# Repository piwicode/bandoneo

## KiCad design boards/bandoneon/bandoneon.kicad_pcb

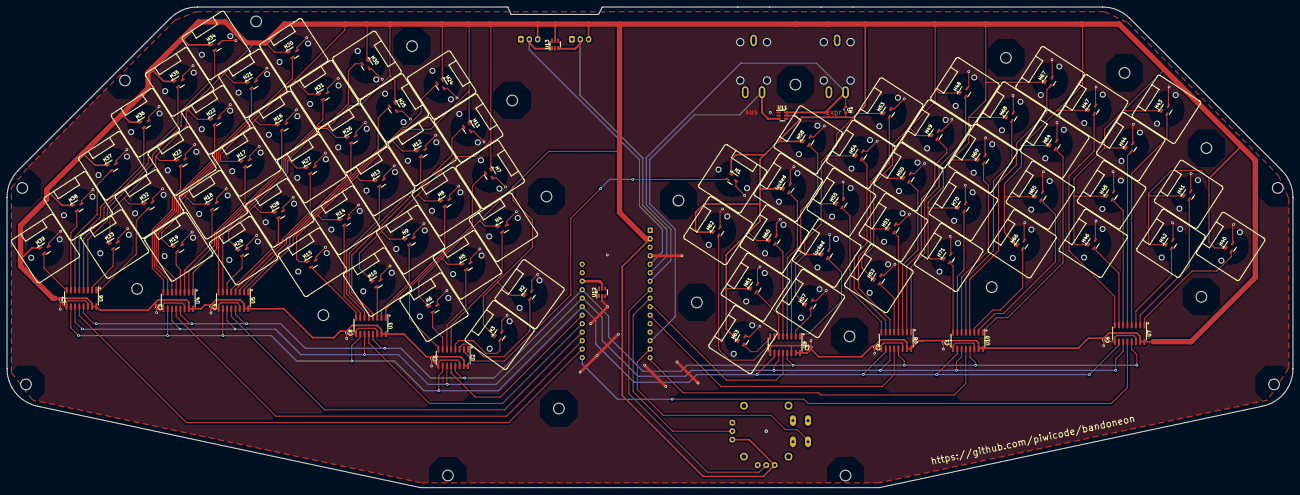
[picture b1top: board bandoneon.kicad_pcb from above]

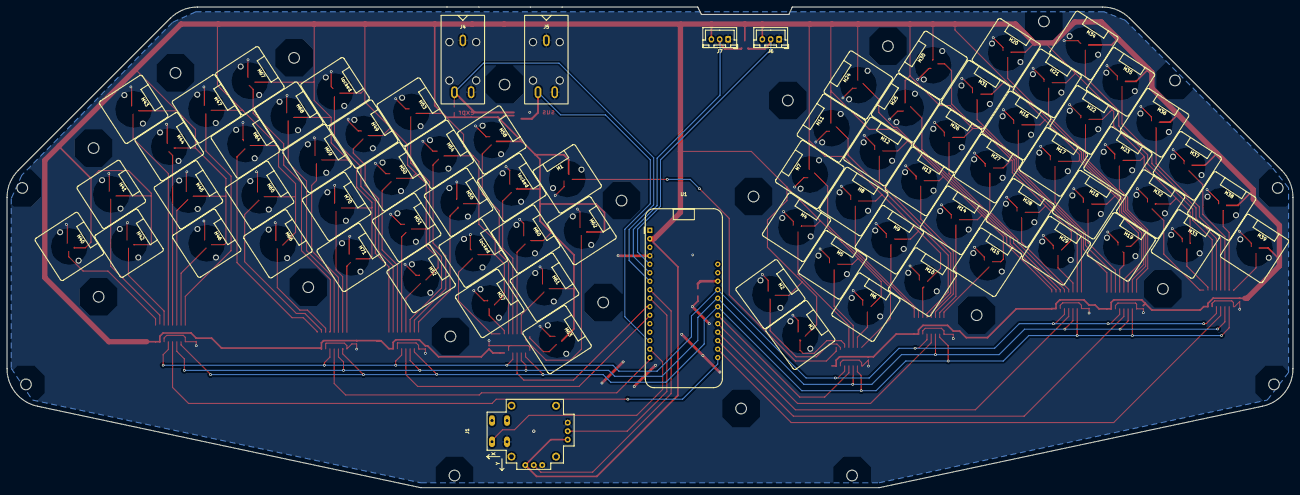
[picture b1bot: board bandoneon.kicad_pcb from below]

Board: 2 copper layers, 384.9 x 143.8 mm, 122 parts (6 on the bottom side), 93 nets.

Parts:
C1, C2, C3, C4, C5, C6, C7, C8, C9: 1uF; C_0402_1005Metric
H1, H2, H3, H4, H5, H6, H7, H8, H9, H10, H11, H12, H13, H14, H15, H16, H17, H18, H19, H20, H21, H22, H23, H24, H25, H26, H27, H28, H29, H30, H31, H32, H33, H34, H35, H36, H37, H38, H39, H40, H41, H42, H43, H44, H45, H46, H47, H48, H49, H50, H51, H52, H53, H54, H55, H57, H58, H60, H61, H62, H63, H64, H65, H66, H67, H68, H69, H70, H71: SS39ET; SOT-23_SS39ET
J1: 2D JOYSTICK; Adafruit (512) Analog 2-axis Thumb Joystick with Select But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
J4, J5: AudioJack3; Jack TRS
J6, J7: JST XH-3A; JST_XH_B3B-XH-A_1x03_P2.50mm_Vertical
MH01, MH02, MH03, MH05, MH06, MH07, MH08, MH09, MH10, MH11, MH12, MH13, MH14, MH15, MH16, MH17, MH18, MH19, MH20, MH21, MH22, MH33, MH39: MountingHole_3.2mm_M3_large
R1: 10K; R_0603_1608Metric
U1: Feather M4 Express; Adafruit_Feather_M4_Express
U2, U3, U4, U5, U6, U7, U8, U9, U10: MCP3008; SOIC-16_MCP3008T-I_SL
U11, U12, U13: SRV05-4; SOT-23-6
locked: SS39ET; SOT-23_SS39ET
locked#2: locked; SOT-23_SS39ET

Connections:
+3.3V: C1.1, C2.1, C3.1, C4.1, C5.1, C6.1, C7.1, C8.1, C9.1, H1.1 (VCC), H2.1 (VCC), H3.1 (VCC), H4.1 (VCC), H5.1 (VCC), H6.1 (VCC), H7.1 (VCC), H8.1 (VCC), H9.1 (VCC), H10.1 (VCC), H11.1 (VCC), H12.1 (VCC), H13.1 (VCC), H14.1 (VCC), H15.1 (VCC), H16.1 (VCC), H17.1 (VCC), H18.1 (VCC), H19.1 (VCC), H20.1 (VCC), H21.1 (VCC), H22.1 (VCC), H23.1 (VCC), H24.1 (VCC), H25.1 (VCC), H26.1 (VCC), H27.1 (VCC), H28.1 (VCC), H29.1 (VCC), H30.1 (VCC), H31.1 (VCC), H32.1 (VCC), H33.1 (VCC), H34.1 (VCC), H35.1 (VCC), H36.1 (VCC), H37.1 (VCC), H38.1 (VCC), H39.1 (VCC), H40.1 (VCC), H41.1 (VCC), H42.1 (VCC), H43.1 (VCC), H44.1 (VCC), H45.1 (VCC), H46.1 (VCC), H47.1 (VCC), H48.1 (VCC), H49.1 (VCC), H50.1 (VCC), H51.1 (VCC), H52.1 (VCC), H53.1 (VCC), H54.1 (VCC), H55.1 (VCC), H57.1 (VCC), H58.1 (VCC), H60.1 (VCC), H61.1 (VCC), H62.1 (VCC), H63.1 (VCC), H64.1 (VCC), H65.1 (VCC), H66.1 (VCC), H67.1 (VCC), H68.1 (VCC), H69.1 (VCC), H70.1 (VCC), H71.1 (VCC), J1.2 (X+), J1.5 (Y+), J6.3, J7.3, R1.2, U1.2 (3.3V), U2.15 (Vref), U2.16 (Vdd), U3.15 (Vref), U3.16 (Vdd), U4.15 (Vref), U4.16 (Vdd), U5.15 (Vref), U5.16 (Vdd), U6.15 (Vref), U6.16 (Vdd), U7.15 (Vref), U7.16 (Vdd), U8.15 (Vref), U8.16 (Vdd), U9.15 (Vref), U9.16 (Vdd), U10.15 (Vref), U10.16 (Vdd), U11.5 (VP), U13.5 (VP), locked.1 (VCC), locked#2.1 (VCC)
/CLK: U1.25 ((13)PA23), U2.13 (CLK), U3.13 (CLK), U4.13 (CLK), U5.13 (CLK), U6.13 (CLK), U7.13 (CLK), U8.13 (CLK), U9.13 (CLK), U10.13 (CLK)
/CS: U1.23 ((11)PA21), U2.10 (~CS/SHDN), U3.10 (~CS/SHDN), U4.10 (~CS/SHDN), U5.10 (~CS/SHDN), U6.10 (~CS/SHDN), U7.10 (~CS/SHDN), U8.10 (~CS/SHDN), U9.10 (~CS/SHDN), U10.10 (~CS/SHDN)
/EXPR_PED: J4.T, R1.1, U1.7 (PB08(16/A2)), U11.6 (IO4)
/G1/MISO: U1.22 ((10)PA20), U2.12 (Dout)
/G2/MISO: U1.21 ((9)PA19), U3.12 (Dout)
/G3/MISO: U1.19 ((5)PA16), U4.12 (Dout)
/G4/MISO: U1.20 ((6)PA18), U5.12 (Dout)
/G5/MISO: U1.18 ((22)PA13), U6.12 (Dout)
/G6/MISO: U1.16 (PA14(4)), U10.12 (Dout)
/G7/MISO: U1.10 (PA06(19/A5)), U9.12 (Dout)
/G9/MISO: U1.17 ((21)PA12), U7.12 (Dout)
/G10/MISO: U1.11 (PA17(25)), U8.12 (Dout)
/JOY_BT: J1.7 (BTN+), U1.15 (PB16(1))
/JOY_X: J1.1 (X), U1.8 (PB09(17/A3))
/JOY_Y: J1.4 (Y), U1.9 (PA04(18/A4))
/MOSI: U1.24 ((12)PA22), U2.11 (Din), U3.11 (Din), U4.11 (Din), U5.11 (Din), U6.11 (Din), U7.11 (Din), U8.11 (Din), U9.11 (Din), U10.11 (Din)
/P1: J7.2, U1.6 (PA05(15/A1)), U13.3 (IO2)
/P2: J6.2, U1.5 (PA02(14/A0)), U13.1 (IO1)
/SUS_PED: J5.T, U1.14 (PB17(0)), U11.3 (IO2)
/VBUS: U1.26 (VBUS), U12.5 (VP)
GND: C1.2, C2.2, C3.2, C4.2, C5.2, C6.2, C7.2, C8.2, C9.2, H1.3 (GND), H2.3 (GND), H3.3 (GND), H4.3 (GND), H5.3 (GND), H6.3 (GND), H7.3 (GND), H8.3 (GND), H9.3 (GND), H10.3 (GND), H11.3 (GND), H12.3 (GND), H13.3 (GND), H14.3 (GND), H15.3 (GND), H16.3 (GND), H17.3 (GND), H18.3 (GND), H19.3 (GND), H20.3 (GND), H21.3 (GND), H22.3 (GND), H23.3 (GND), H24.3 (GND), H25.3 (GND), H26.3 (GND), H27.3 (GND), H28.3 (GND), H29.3 (GND), H30.3 (GND), H31.3 (GND), H32.3 (GND), H33.3 (GND), H34.3 (GND), H35.3 (GND), H36.3 (GND), H37.3 (GND), H38.3 (GND), H39.3 (GND), H40.3 (GND), H41.3 (GND), H42.3 (GND), H43.3 (GND), H44.3 (GND), H45.3 (GND), H46.3 (GND), H47.3 (GND), H48.3 (GND), H49.3 (GND), H50.3 (GND), H51.3 (GND), H52.3 (GND), H53.3 (GND), H54.3 (GND), H55.3 (GND), H57.3 (GND), H58.3 (GND), H60.3 (GND), H61.3 (GND), H62.3 (GND), H63.3 (GND), H64.3 (GND), H65.3 (GND), H66.3 (GND), H67.3 (GND), H68.3 (GND), H69.3 (GND), H70.3 (GND), H71.3 (GND), J1.0 (X-), J1.3 (Y-), J1.6 (BTN-), J4.R, J4.S, J5.R, J5.S, J6.1, J7.1, U1.4 (GND), U2.9 (DGND), U2.14 (AGND), U3.9 (DGND), U3.14 (AGND), U4.9 (DGND), U4.14 (AGND), U5.9 (DGND), U5.14 (AGND), U6.9 (DGND), U6.14 (AGND), U7.9 (DGND), U7.14 (AGND), U8.9 (DGND), U8.14 (AGND), U9.9 (DGND), U9.14 (AGND), U10.9 (DGND), U10.14 (AGND), U11.2 (VN), U12.2 (VN), U13.2 (VN), locked.3 (GND), locked#2.3 (GND)
unnamed: H1.2 (OUT), U2.2 (CH1)
unnamed: H2.2 (OUT), U2.3 (CH2)
unnamed: H3.2 (OUT), U2.4 (CH3)
unnamed: H4.2 (OUT), U2.5 (CH4)
unnamed: H5.2 (OUT), U2.6 (CH5)
unnamed: H6.2 (OUT), U2.7 (CH6)
unnamed: H7.2 (OUT), U2.8 (CH7)
unnamed: H8.2 (OUT), U3.1 (CH0)
unnamed: H9.2 (OUT), U3.2 (CH1)
unnamed: H10.2 (OUT), U3.3 (CH2)
unnamed: H11.2 (OUT), U3.4 (CH3)
unnamed: H12.2 (OUT), U3.5 (CH4)
unnamed: H13.2 (OUT), U3.6 (CH5)
unnamed: H14.2 (OUT), U3.7 (CH6)
unnamed: H15.2 (OUT), U3.8 (CH7)
unnamed: H16.2 (OUT), U4.1 (CH0)
unnamed: H17.2 (OUT), U4.2 (CH1)
unnamed: H18.2 (OUT), U4.3 (CH2)
unnamed: H19.2 (OUT), U4.4 (CH3)
unnamed: H20.2 (OUT), U4.5 (CH4)
unnamed: H21.2 (OUT), U4.6 (CH5)
unnamed: H22.2 (OUT), U4.7 (CH6)
unnamed: H23.2 (OUT), U4.8 (CH7)
unnamed: H24.2 (OUT), U5.1 (CH0)
unnamed: H25.2 (OUT), U5.2 (CH1)
unnamed: H26.2 (OUT), U5.3 (CH2)
unnamed: H27.2 (OUT), U5.4 (CH3)
unnamed: H28.2 (OUT), U5.5 (CH4)
unnamed: H29.2 (OUT), U5.6 (CH5)
unnamed: H30.2 (OUT), U5.7 (CH6)
unnamed: H31.2 (OUT), U5.8 (CH7)
unnamed: H32.2 (OUT), U6.1 (CH0)
unnamed: H33.2 (OUT), U6.2 (CH1)
unnamed: H34.2 (OUT), U6.3 (CH2)
unnamed: H35.2 (OUT), U6.4 (CH3)
unnamed: H36.2 (OUT), U6.5 (CH4)
unnamed: H37.2 (OUT), U6.6 (CH5)
unnamed: H38.2 (OUT), U6.7 (CH6)
unnamed: H39.2 (OUT), U6.8 (CH7)
unnamed: H40.2 (OUT), U7.1 (CH0)
unnamed: H41.2 (OUT), U7.2 (CH1)
unnamed: H42.2 (OUT), U7.3 (CH2)
unnamed: H43.2 (OUT), U7.4 (CH3)
unnamed: H44.2 (OUT), U7.5 (CH4)
unnamed: H45.2 (OUT), U7.6 (CH5)
unnamed: H46.2 (OUT), U7.7 (CH6)
unnamed: H47.2 (OUT), U7.8 (CH7)
unnamed: H48.2 (OUT), U8.1 (CH0)
unnamed: H49.2 (OUT), U8.2 (CH1)
unnamed: H50.2 (OUT), U8.3 (CH2)
unnamed: H51.2 (OUT), U8.4 (CH3)
unnamed: H52.2 (OUT), U8.5 (CH4)
unnamed: H53.2 (OUT), U8.6 (CH5)
unnamed: H54.2 (OUT), U8.7 (CH6)
unnamed: H55.2 (OUT), U8.8 (CH7)
unnamed: U9.1 (CH0), locked#2.2 (OUT)
unnamed: H57.2 (OUT), U9.2 (CH1)
unnamed: H58.2 (OUT), U9.3 (CH2)
unnamed: U9.4 (CH3), locked.2 (OUT)
unnamed: H60.2 (OUT), U9.5 (CH4)
unnamed: H61.2 (OUT), U9.6 (CH5)
unnamed: H62.2 (OUT), U9.7 (CH6)
unnamed: H63.2 (OUT), U9.8 (CH7)
unnamed: H64.2 (OUT), U10.1 (CH0)
unnamed: H65.2 (OUT), U10.2 (CH1)
unnamed: H66.2 (OUT), U10.3 (CH2)
unnamed: H67.2 (OUT), U10.4 (CH3)
unnamed: H68.2 (OUT), U10.5 (CH4)
unnamed: H69.2 (OUT), U10.6 (CH5)
unnamed: H70.2 (OUT), U10.7 (CH6)
unnamed: H71.2 (OUT), U10.8 (CH7)

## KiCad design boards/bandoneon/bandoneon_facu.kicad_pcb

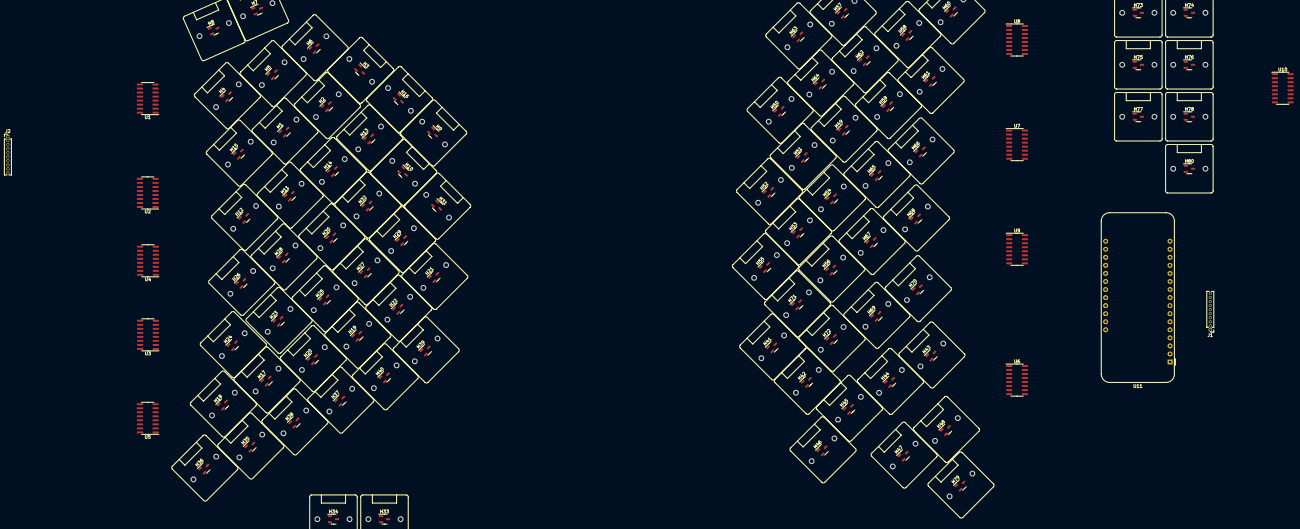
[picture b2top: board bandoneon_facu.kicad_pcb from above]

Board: 2 copper layers, 93 parts (0 on the bottom side), 105 nets, no tracks yet.

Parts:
H1, H2, H3, H4, H5, H6, H7, H8, H9, H10, H11, H12, H13, H14, H15, H16, H17, H18, H19, H20, H21, H22, H23, H24, H25, H26, H27, H28, H29, H30, H31, H32, H33, H34, H35, H36, H37, H38, H39, H40, H41, H42, H43, H44, H45, H46, H47, H48, H49, H50, H51, H52, H53, H54, H55, H56, H57, H58, H59, H60, H61, H62, H63, H64, H65, H66, H67, H68, H69, H70, H71, H72, H73, H74, H75, H76, H77, H78, H79, H80: SS39ET
J1, J2: Conn_01x10_Pin; PinHeader_1x10_P1.27mm_Vertical
U1, U2, U3, U4, U5, U6, U7, U8, U9, U10: MCP3008; MCP3008T-I_SL
U11: Adafruit_Feather_M4_Express

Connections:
+3.3V: H41.1 (VCC), H42.1 (VCC), H43.1 (VCC), H44.1 (VCC), H45.1 (VCC), H46.1 (VCC), H47.1 (VCC), H48.1 (VCC), H49.1 (VCC), H50.1 (VCC), H51.1 (VCC), H52.1 (VCC), H53.1 (VCC), H54.1 (VCC), H55.1 (VCC), H56.1 (VCC), H57.1 (VCC), H58.1 (VCC), H59.1 (VCC), H60.1 (VCC), H61.1 (VCC), H62.1 (VCC), H63.1 (VCC), H64.1 (VCC), H65.1 (VCC), H66.1 (VCC), H67.1 (VCC), H68.1 (VCC), H69.1 (VCC), H70.1 (VCC), H71.1 (VCC), H72.1 (VCC), H73.1 (VCC), H74.1 (VCC), H75.1 (VCC), H76.1 (VCC), H77.1 (VCC), H78.1 (VCC), H79.1 (VCC), H80.1 (VCC), J1.1, U6.15 (Vref), U6.16 (Vdd), U7.15 (Vref), U7.16 (Vdd), U8.15 (Vref), U8.16 (Vdd), U9.15 (Vref), U9.16 (Vdd), U10.15 (Vref), U10.16 (Vdd), U11.2 (3.3V)
/CLK: J1.3, U6.13 (CLK), U7.13 (CLK), U8.13 (CLK), U9.13 (CLK), U10.13 (CLK), U11.25 (PA23)
/CS: J1.5, U6.10 (~CS/SHDN), U7.10 (~CS/SHDN), U8.10 (~CS/SHDN), U9.10 (~CS/SHDN), U10.10 (~CS/SHDN), U11.23 (PA21)
/G1/MISO: J2.10, U1.12 (Dout)
/G2/MISO: J2.9, U2.12 (Dout)
/G3/MISO: J2.8, U3.12 (Dout)
/G4/MISO: J2.7, U4.12 (Dout)
/G5/MISO: J2.6, U5.12 (Dout)
/G6/MISO: U9.12 (Dout), U11.19 (PA16)
/G7/MISO: U8.12 (Dout), U11.20 (PA18)
/G8/MISO: U10.12 (Dout), U11.18 (PA13)
/G9/MISO: U6.12 (Dout), U11.22 (PA20)
/G10/MISO: U7.12 (Dout), U11.21 (PA19)
/MOSI: J1.4, U6.11 (Din), U7.11 (Din), U8.11 (Din), U9.11 (Din), U10.11 (Din), U11.24 (PA22)
/R_3V3: H1.1 (VCC), H2.1 (VCC), H3.1 (VCC), H4.1 (VCC), H5.1 (VCC), H6.1 (VCC), H7.1 (VCC), H8.1 (VCC), H9.1 (VCC), H10.1 (VCC), H11.1 (VCC), H12.1 (VCC), H13.1 (VCC), H14.1 (VCC), H15.1 (VCC), H16.1 (VCC), H17.1 (VCC), H18.1 (VCC), H19.1 (VCC), H20.1 (VCC), H21.1 (VCC), H22.1 (VCC), H23.1 (VCC), H24.1 (VCC), H25.1 (VCC), H26.1 (VCC), H27.1 (VCC), H28.1 (VCC), H29.1 (VCC), H30.1 (VCC), H31.1 (VCC), H32.1 (VCC), H33.1 (VCC), H34.1 (VCC), H35.1 (VCC), H36.1 (VCC), H37.1 (VCC), H38.1 (VCC), H39.1 (VCC), H40.1 (VCC), J2.1, U1.15 (Vref), U1.16 (Vdd), U2.15 (Vref), U2.16 (Vdd), U3.15 (Vref), U3.16 (Vdd), U4.15 (Vref), U4.16 (Vdd), U5.15 (Vref), U5.16 (Vdd)
/R_CLK: J2.3, U1.13 (CLK), U2.13 (CLK), U3.13 (CLK), U4.13 (CLK), U5.13 (CLK)
/R_CS: J2.5, U1.10 (~CS/SHDN), U2.10 (~CS/SHDN), U3.10 (~CS/SHDN), U4.10 (~CS/SHDN), U5.10 (~CS/SHDN)
/R_GND: H1.3 (GND), H2.3 (GND), H3.3 (GND), H4.3 (GND), H5.3 (GND), H6.3 (GND), H7.3 (GND), H8.3 (GND), H9.3 (GND), H10.3 (GND), H11.3 (GND), H12.3 (GND), H13.3 (GND), H14.3 (GND), H15.3 (GND), H16.3 (GND), H17.3 (GND), H18.3 (GND), H19.3 (GND), H20.3 (GND), H21.3 (GND), H22.3 (GND), H23.3 (GND), H24.3 (GND), H25.3 (GND), H26.3 (GND), H27.3 (GND), H28.3 (GND), H29.3 (GND), H30.3 (GND), H31.3 (GND), H32.3 (GND), H33.3 (GND), H34.3 (GND), H35.3 (GND), H36.3 (GND), H37.3 (GND), H38.3 (GND), H39.3 (GND), H40.3 (GND), J2.2, U1.9 (DGND), U1.14 (AGND), U2.9 (DGND), U2.14 (AGND), U3.9 (DGND), U3.14 (AGND), U4.9 (DGND), U4.14 (AGND), U5.9 (DGND), U5.14 (AGND)
/R_MOSI: J2.4, U1.11 (Din), U2.11 (Din), U3.11 (Din), U4.11 (Din), U5.11 (Din)
GND: H41.3 (GND), H42.3 (GND), H43.3 (GND), H44.3 (GND), H45.3 (GND), H46.3 (GND), H47.3 (GND), H48.3 (GND), H49.3 (GND), H50.3 (GND), H51.3 (GND), H52.3 (GND), H53.3 (GND), H54.3 (GND), H55.3 (GND), H56.3 (GND), H57.3 (GND), H58.3 (GND), H59.3 (GND), H60.3 (GND), H61.3 (GND), H62.3 (GND), H63.3 (GND), H64.3 (GND), H65.3 (GND), H66.3 (GND), H67.3 (GND), H68.3 (GND), H69.3 (GND), H70.3 (GND), H71.3 (GND), H72.3 (GND), H73.3 (GND), H74.3 (GND), H75.3 (GND), H76.3 (GND), H77.3 (GND), H78.3 (GND), H79.3 (GND), H80.3 (GND), J1.2, U6.9 (DGND), U6.14 (AGND), U7.9 (DGND), U7.14 (AGND), U8.9 (DGND), U8.14 (AGND), U9.9 (DGND), U9.14 (AGND), U10.9 (DGND), U10.14 (AGND), U11.4 (GND)
unnamed: H1.2 (OUT), U1.1 (CH0)
unnamed: H2.2 (OUT), U1.2 (CH1)
unnamed: H3.2 (OUT), U1.3 (CH2)
unnamed: H4.2 (OUT), U1.4 (CH3)
unnamed: H5.2 (OUT), U1.5 (CH4)
unnamed: H6.2 (OUT), U1.6 (CH5)
unnamed: H7.2 (OUT), U1.7 (CH6)
unnamed: H8.2 (OUT), U1.8 (CH7)
unnamed: H9.2 (OUT), U2.1 (CH0)
unnamed: H10.2 (OUT), U2.2 (CH1)
unnamed: H11.2 (OUT), U2.3 (CH2)
unnamed: H12.2 (OUT), U2.4 (CH3)
unnamed: H13.2 (OUT), U2.5 (CH4)
unnamed: H14.2 (OUT), U2.6 (CH5)
unnamed: H15.2 (OUT), U2.7 (CH6)
unnamed: H16.2 (OUT), U2.8 (CH7)
unnamed: H17.2 (OUT), U3.1 (CH0)
unnamed: H18.2 (OUT), U3.2 (CH1)
unnamed: H19.2 (OUT), U3.3 (CH2)
unnamed: H20.2 (OUT), U3.4 (CH3)
unnamed: H21.2 (OUT), U3.5 (CH4)
unnamed: H22.2 (OUT), U3.6 (CH5)
unnamed: H23.2 (OUT), U3.7 (CH6)
unnamed: H24.2 (OUT), U3.8 (CH7)
unnamed: H25.2 (OUT), U4.1 (CH0)
unnamed: H26.2 (OUT), U4.2 (CH1)
unnamed: H27.2 (OUT), U4.3 (CH2)
unnamed: H28.2 (OUT), U4.4 (CH3)
unnamed: H29.2 (OUT), U4.5 (CH4)
unnamed: H30.2 (OUT), U4.6 (CH5)
unnamed: H31.2 (OUT), U4.7 (CH6)
unnamed: H32.2 (OUT), U4.8 (CH7)
unnamed: H33.2 (OUT), U5.1 (CH0)
unnamed: H34.2 (OUT), U5.2 (CH1)
unnamed: H35.2 (OUT), U5.3 (CH2)
unnamed: H36.2 (OUT), U5.4 (CH3)
unnamed: H37.2 (OUT), U5.5 (CH4)
unnamed: H38.2 (OUT), U5.6 (CH5)
unnamed: H39.2 (OUT), U5.7 (CH6)
unnamed: H40.2 (OUT), U5.8 (CH7)
unnamed: H41.2 (OUT), U6.1 (CH0)
unnamed: H42.2 (OUT), U6.2 (CH1)
unnamed: H43.2 (OUT), U6.3 (CH2)
unnamed: H44.2 (OUT), U6.4 (CH3)
unnamed: H45.2 (OUT), U6.5 (CH4)
unnamed: H46.2 (OUT), U6.6 (CH5)
unnamed: H47.2 (OUT), U6.7 (CH6)
unnamed: H48.2 (OUT), U6.8 (CH7)
unnamed: H49.2 (OUT), U7.1 (CH0)
unnamed: H50.2 (OUT), U7.2 (CH1)
unnamed: H51.2 (OUT), U7.3 (CH2)
unnamed: H52.2 (OUT), U7.4 (CH3)
unnamed: H53.2 (OUT), U7.5 (CH4)
unnamed: H54.2 (OUT), U7.6 (CH5)
unnamed: H55.2 (OUT), U7.7 (CH6)
unnamed: H56.2 (OUT), U7.8 (CH7)
unnamed: H57.2 (OUT), U8.1 (CH0)
unnamed: H58.2 (OUT), U8.2 (CH1)
unnamed: H59.2 (OUT), U8.3 (CH2)
unnamed: H60.2 (OUT), U8.4 (CH3)
unnamed: H61.2 (OUT), U8.5 (CH4)
unnamed: H62.2 (OUT), U8.6 (CH5)
unnamed: H63.2 (OUT), U8.7 (CH6)
unnamed: H64.2 (OUT), U8.8 (CH7)
unnamed: H65.2 (OUT), U9.1 (CH0)
unnamed: H66.2 (OUT), U9.2 (CH1)
unnamed: H67.2 (OUT), U9.3 (CH2)
unnamed: H68.2 (OUT), U9.4 (CH3)
unnamed: H69.2 (OUT), U9.5 (CH4)
unnamed: H70.2 (OUT), U9.6 (CH5)
unnamed: H71.2 (OUT), U9.7 (CH6)
unnamed: H72.2 (OUT), U9.8 (CH7)
unnamed: H73.2 (OUT), U10.1 (CH0)
unnamed: H74.2 (OUT), U10.2 (CH1)
unnamed: H75.2 (OUT), U10.3 (CH2)
unnamed: H76.2 (OUT), U10.4 (CH3)
unnamed: H77.2 (OUT), U10.5 (CH4)
unnamed: H78.2 (OUT), U10.6 (CH5)
unnamed: H79.2 (OUT), U10.7 (CH6)
unnamed: H80.2 (OUT), U10.8 (CH7)
unnamed: J1.6, U11.5 (PA02)
unnamed: J1.7, U11.6 (PA05)
unnamed: J1.8, U11.9 (PA04)
unnamed: J1.9, U11.10 (PA06)
unnamed: J1.10, U11.11 (PA17)

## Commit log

2024-01-18 Blink program
2024-01-19 Midi experiments.
2024-01-19 Read MCP inputs.
2024-01-19 Software SPI
2024-01-20 Sucessfull bitback on a single channel.
2024-01-21 Document bitbanging naive attempt.
2024-01-21 Benchmark IO
2024-01-21 Pad write update.
2024-01-21 Remove merger tag
2024-01-22 Fix output register
2024-01-22 Optimize IO leveraging OUTSET and OUTCLEAR registers.
2024-01-23 Improve readme.
2024-01-23 Optimize SPI
2024-01-24 images
2024-01-26 Scan 40 sensors
2024-01-27 Update readme.
2024-01-27 Add instrument sources.
2024-01-30 Add boards
2024-01-30 Git ignore
2024-01-31 Design the board layout in kicad
2024-01-31 Design a cap
2024-01-31 Update positionning pins spacing to .4 in
2024-02-04 Add key caps with various inner size
2024-02-04 Remove pcb copy
2024-02-04 Use keyboard layout and set images DPI
2024-02-04 Fix mathjax expression
2024-02-10 Schamtic complete
2024-02-10 Fix component side
2024-02-10 More datasheets
2024-02-15 Printing carter attempt.
2024-02-16 slicer screenshot
2024-02-16 Document cap printing
2024-02-16 Add cap v2
2024-02-26 Add 1cm between two keyboards and ready for print test.
2024-02-26 Add strap screws
2024-02-26 Addjust holes with various sizes
2024-02-26 Larger Joystick hole
2024-03-01 Adjust caps
2024-03-01 Adjust joystick and model jack
2024-03-07 Schema before wiring
2024-03-08 PCB Check clear
2024-03-08 Ready for routing
2024-03-10 Manual routing
2024-03-10 Fix refs before autoroute
2024-03-10 Add models and ground plane
2024-03-11 Complete manual wire
2024-03-11 Import back enforce
2024-03-13 Add JCLPCB script
2024-03-14 Wiring fixed
2024-03-14 Ready for review
2024-03-16 More models.
2024-03-17 Add esd protection
2024-03-18 Ready for print
2024-03-18 Add screw and glue surface
2024-03-18 More glue surface.
2024-03-26 Before setting up the bom + pick and place
2024-03-27 Gerber and bom export
2024-03-28 Ready for fabrication
2024-03-30 PCB order
2024-03-30 Assembled breadboard test
2024-04-06 Program update on printed board.
2024-04-07 Fix jack footprint and wiring.
2024-04-07 Add joystick and potentiometers support.
2024-04-07 Fix support and add pockets for pins
2024-04-13 Explain production steps.
2024-04-13 Use one MIDI channel per hand.
2024-04-19 Add more const.
2024-04-19 Remove step.
2024-04-22 Add nrf52 + analog swich POC.
2024-04-28 3dprint unsplit
2024-04-30 Give up printing as a single part.
2024-05-20 Add sustain, reduce sensitivity, change btns direction
2024-05-20 Annotate TRS.
2024-05-22 Fix potentimeter glitchm and add neopixel support
2025-07-13 Document processor selection.
2025-07-27 Start to build the motherboard.
2025-07-27 Design main board.
2025-07-27 Add license.md
2025-09-05 Import bandoneon pictures.
2025-09-10 Add grid paper PostScript
2025-09-11 Grid paper is now aliased on printer dotmatrix.
    Now thinlines are rendered correctly on Bother lazer printer.
    The scaling with `lpr -o raw` print command is correct on the short edge
    but slightly stretched (150.6 mm for 150.0 mm) on the long edge.
    Also the pattern is not centered anymore for simplification.
2025-09-11 [gridpaper] Add scale factors to compasate for the printer.
2025-09-11 [gridpaper] Add proper licensing.
2025-09-11 Add bandoneon keyboard and handle pictures.
2025-09-14 Experimental keyboard placement scripts.
2025-09-14 Adjust scale facore to my printer. This produces precise prints.
2025-09-14 PCB with fairly good placements.
2025-09-22 [pcb] drill support hole in PCB
2025-09-22 [pcb] Fix hall sensor count
2025-09-22 [pcb] Make boards the same
2025-09-22 [pcb] Bind unused pins.
2025-09-22 [pcb] Reannotate components.
2025-09-23 [pcb] Pulldown every floading.
2025-09-23 [pcb] document protocol.
2025-09-24 [pcb] wire right wing
2025-09-26 Add license.
2025-09-26 minor update
2025-10-04 [pcb] Reassign pins to reserve powerfull pins for future use.
2025-10-05 [pcb] Right wing wired except GND
2025-10-05 [pcb] Right wing complete
2025-10-06 [pcb] right wing DRC ok.
2025-10-06 [pcb] left wing wired, except gnd.
2025-10-07 [pcb] Both wings wired with no DRC error.
2025-10-08 [pcb] Improved naming, fixed led resistor.
2025-10-10 [pcb] power block of the mother board.
2025-11-23 More notes
2025-12-19 USB notes
2025-12-27 Document USB
2025-12-27 Initial code generation for nucleo-wb55rg
2025-12-27 Enable SWO trace and override printf.
2025-12-29 Enable USB hardware without middleware.
    Also fixed clock issues with automatic resolution.
    Also updated SWO frequency.
2025-12-29 Add TinyUSB Integration with STM32HAL.
    For TinyUSB only include the portable/st/stm32_fsdev
    The list can be found in the bsp cmakefile.
2025-12-30 Enable USB on WBA board configuration.
    For STM32WBA65, open the `.ioc` file and then:
    1. Go to `System Core` > `GPIO` (also known as `General Input Output`), select
    tab `RCC` (`Reset and Clock Control`)
    2. Bind pin `OSC_IN` to signal `RCC_OSC_IN` and `OSC_OUT` to `RCC_OSC_OUT`.
    3. Go to `Connectivity` > `USB_OTG_HS` (OTG means Over The Go which indicates
    the processor can either be a device or a host, and HS means Hish Speed which
2025-12-30 Update eclipse projects git ignore.
2025-12-30 Add stm32wba65 nucleo board project.
    Also implement SWO traces.
2025-12-30 USB responsive on WBA65RI.
    Added USB Logs.
2025-12-31 Send USB midi messages.
2026-01-07 Generate code for BT service
2026-04-12 Experiment with stm32
2026-04-12 Update hall effect sensor
2026-04-17 Better TSD protection
2026-04-20 ESD review done
2026-04-20 Fix hal switch migration
2026-04-20 Review power line and apply mino adjustments
2026-04-20 Netlist and ioc consolidation script.
2026-04-20 Create fn buttons.
2026-04-20 main board review
2026-04-21 Use boot0 as FN3 to allow user DFU
2026-04-21 Add shortcut protection to the bandoneo wing ports.
2026-04-22 Polish wing left
2026-04-22 Same Left and right wing schema.
2026-04-22 Prepare design review
2026-04-22 Complete hall sensord migration
2026-04-22 Prevent backfeeding with buffers.
2026-04-26 Two pressure prototypes
2026-05-02 Add pogo pins and script pricing
2026-05-03 Update connectors and designators of main sheet
2026-05-04 Prepare centring hall sensors
2026-05-04 Fixed hall sensor placement
2026-05-04 Fix main hall footprint
2026-05-04 Fix DRC and make pinout consistent.
2026-05-05 Layout mainboard switches
2026-05-05 Layout power
2026-05-19 Update schmatics with not batteries
2026-05-19 Schema complete.
2026-05-21 Prepare connector change
2026-05-21 New connectors done.
2026-05-26 Rewire left board
2026-05-27 Connector aligned
2026-05-28 main board ready
2026-05-29 Wiring readay for final review
2026-05-30 Ready for panelisation
2026-05-31 Production files v1.0-alpha
2026-05-31 Remove soldering paste on landing patterns
2026-05-31 Move VCC via out of main landing pattern pad
2026-06-01 Fix left wing perimeter to be horizontal.
2026-06-06 Reposition labels on silkscreen
2026-06-08 Remove obsolete board configuration
2026-06-08 Adjust main board GPIO settings in IOC.
2026-06-08 Generate main board code.
2026-06-09 Fix SWO tracing with STLINK-V3.
2026-06-09 Introduce 'just' recipe cookbook command line tool.
2026-06-09 Configure git to deal with CRLF generated by STM tooling.
2026-06-09 Add USART console output.
2026-06-09 Add repl on pgm usart.
2026-06-09 Add reset and trace_swo just commands
2026-06-09 Configure vscode to build and test.
2026-06-09 Board: Fix function leds inverted polarity.
2026-06-09 Use CRLF on usart output. Inject CR automatically.
    Rename shell library to console.
2026-06-09 Fix compliation headerlist.
2026-06-09 [Board] Minor layout improvement.
2026-06-09 Pedal reading and logging ok.
2026-06-09 Set HALL_NEN as open drain and generate code.
    There is a pull up resistor on the board that just needs
    to be shorted to ground.
2026-06-09 Exercise hall sensors with success
2026-06-09 Generate code for the wing.
    Also share the just scripts.
2026-06-09 Add a safety for flashing boards.
    A listing associates MCU id to a board type to
    prevent flashing the wrong board image which could
    cause troubles with GPIO.
2026-06-09 Make build vscode command depend on the current file.
2026-06-09 Add console to the wing.
2026-06-09 Fix compilation in vscode
2026-06-09 [wing] Read and show function button.
2026-06-09 [wing] Blink leds.
2026-06-09 Naive keyboard scanning.
2026-06-10 Verify USART NVIC configuration.
2026-06-10 Benchmark various parallel ADC acquisition.
2026-06-10 Add `just release` command to flash opt code.
    It inits builds and flash optimised code which
    goes 2.3 x faster on adc sampling.
2026-06-10 Fix VCC rail tracks dimensions.
2026-06-11 Now wings are masters and main is slave.
    Also add a test for consistency checkgin for SPI definitions.
2026-06-11 USB Midi support.
    Rearrange the clocks to use HSI48 which has RRC to selfcorrect
    using host clock.
    Also run all mcu at 96 MHz, which is divided by 2 for ADC clock.
    48 MHz is closeto the maximum of 52 MHz in the datasheet:
    "Range 1, all ADCs operation, single ended mode VDDA ≥ 2.7 V"
2026-06-11 Update gitignot and clangd configuration.
2026-06-11 Only keep DMS scanning of ADCs
    for the record:
    naive polling : 95910 cycles ( 999.062 us) min= 0 max=2568 free=125.9 KiB
    parallel polling: 88422 cycles ( 921.062 us) min= 0 max=2567 free=125.9 KiB
    dma scan : 16952 cycles ( 176.583 us) min= 0 max=2579 free=125.9 KiB
2026-06-11 Simplify ADC setup.
2026-06-11 Add statistics for key press.
2026-06-11 Increase USART speed
2026-06-11 Add key press detection and frame build.
2026-06-11 Push keypress to SPI buss
2026-06-12 Partially working bus.
2026-06-12 Implement keyboard mapping.
2026-06-12 Make main code wing agnostic.
2026-06-12 Implement push pull on key mapping
2026-06-12 Enable bellows. Functionnal instrument.
